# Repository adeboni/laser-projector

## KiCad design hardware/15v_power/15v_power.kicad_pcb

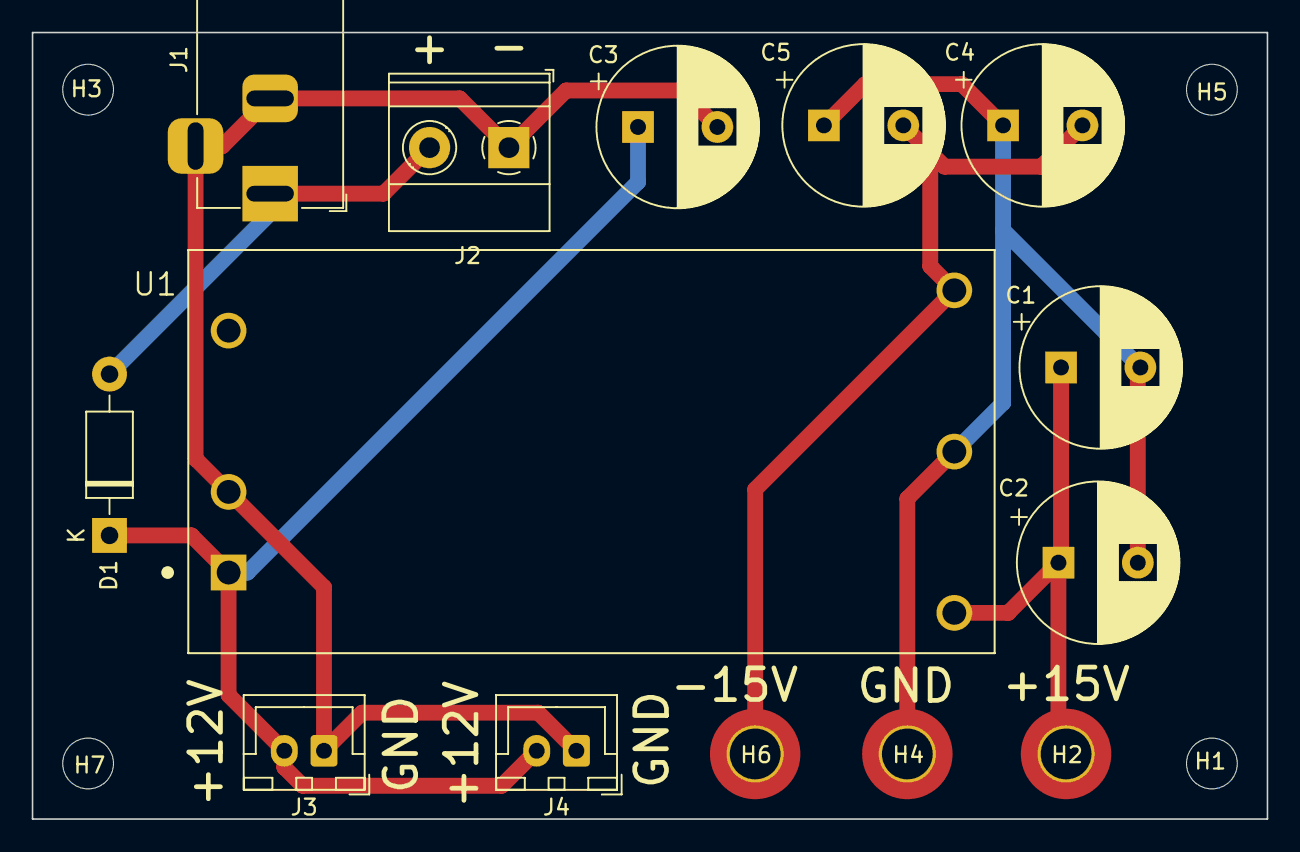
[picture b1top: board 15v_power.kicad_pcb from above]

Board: 2 copper layers, 77.8 x 49.5 mm, 18 parts (0 on the bottom side), 6 nets.

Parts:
C1, C2, C3, C4, C5: 220u; CP_Radial_D10.0mm_P5.00mm
D1: 1N4007; D_DO-41_SOD81_P10.16mm_Horizontal
H1, H3, H5, H7: MountingHole; MountingHole_3.2mm_M3
H2, H4, H6: MountingHole_Pad; MountingHole_3.2mm_M3_ISO7380_Pad_TopBottom
J1: Barrel_Jack_Switch; BarrelJack_Horizontal
J2: Screw_Terminal_01x02; TerminalBlock_Phoenix_MKDS-1,5-2_1x02_P5.00mm_Horizontal
J3, J4: Conn_01x02; JST_XH_B2B-XH-A_1x02_P2.50mm_Vertical
U1: TEN20-2422WIN; CONV_PYBE30-Q24-D12

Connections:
+15V: C1.1, C2.1, H2.1, U1.6 (VOUT+)
-15V: C4.2, C5.2, H6.1, U1.4 (VOUT-)
GND: C1.2, C2.2, C4.1, C5.1, H4.1, U1.5 (CM)
unnamed: C3.1, D1.1 (K), J3.2, J4.2, U1.1 (VIN+)
unnamed: C3.2, J1.2, J1.3, J2.1, J3.1, J4.1, U1.2 (VIN-)
unnamed: D1.2 (A), J1.1, J2.2

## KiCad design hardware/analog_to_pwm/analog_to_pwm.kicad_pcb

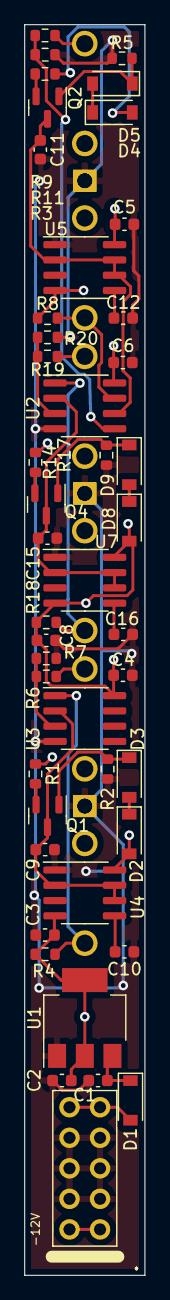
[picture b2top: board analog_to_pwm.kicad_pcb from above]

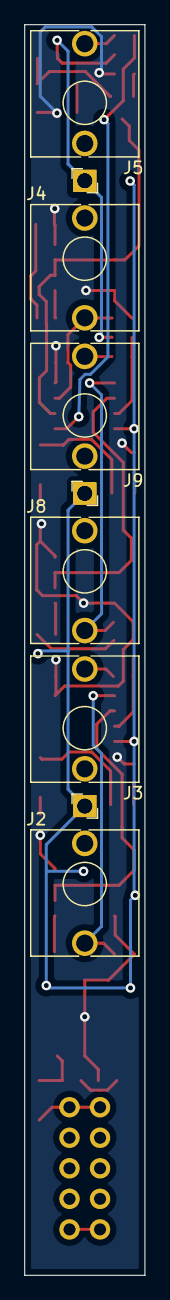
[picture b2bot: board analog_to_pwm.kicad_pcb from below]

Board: 2 copper layers, 10.0 x 104.0 mm, 51 parts (6 on the bottom side), 29 nets.

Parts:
C1, C2: 10u; C_0603_1608Metric
C3, C4, C5, C6, C8, C10, C12, C16: 100n; C_0603_1608Metric
C9, C11, C15: 1.5n; C_0603_1608Metric
D1: SM4007; D_SOD-123
D2, D3, D4, D5, D8, D9: 1N4148W; D_SOD-123
J1: .; Pins_2x05_2.54mm_TH_Europower
J2, J3, J4, J5, J8, J9: JACK; Jack_3.5mm_QingPu_WQP-PJ398SM_Vertical_CircularHoles
Q1, Q2, Q4: MMBT3906; SOT-23
R1, R2, R3, R5, R14, R17: 1k; R_0603_1608Metric
R4, R8, R18: 2.2k; R_0603_1608Metric
R6, R9, R19: 10k; R_0603_1608Metric
R7, R11, R20: 51k; R_0603_1608Metric
U1: LM1117-5.0; SOT-223-3_TabPin2
U2, U3: LM393; SOIC-8_3.9x4.9mm_P1.27mm
U4, U5, U7: NE555D; SOIC-8_3.9x4.9mm_P1.27mm

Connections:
+5V: C2.1, C3.1, C4.1, C5.1, C6.1, C8.1, D2.2 (A), D4.2 (A), D8.2 (A), R1.1, R3.1, R4.1, R8.1, R14.1, R18.1, U1.2 (VO), U2.8 (V+), U3.8 (V+), U4.4 (R), U4.8 (VCC), U5.4 (R), U5.8 (VCC), U7.4 (R), U7.8 (VCC)
GND: C1.2, C2.2, C3.2, C4.2, C5.2, C6.2, C8.2, C9.2, C10.1, C11.2, C12.1, C15.2, C16.1, J1.3, J1.4, J1.5, J1.6, J1.7, J1.8, J2.S, J3.S, J4.S, J5.S, J8.S, J9.S, R2.2, R5.2, R7.2, R11.2, R17.2, R20.2, U1.1 (GND), U2.4 (V-), U3.4 (V-), U4.1 (GND), U5.1 (GND), U7.1 (GND)
unnamed: C1.1, D1.1 (K), U1.3 (VI)
unnamed: C9.1, Q1.3 (C), U3.2 (-), U4.2 (TR), U4.6 (THR), U4.7 (DIS)
unnamed: C10.2, U4.5 (CV)
unnamed: C11.1, Q2.3 (C), U2.6 (_), U5.2 (TR), U5.6 (THR), U5.7 (DIS)
unnamed: C12.2, U5.5 (CV)
unnamed: C15.1, Q4.3 (C), U2.2 (-), U7.2 (TR), U7.6 (THR), U7.7 (DIS)
unnamed: C16.2, U7.5 (CV)
unnamed: D1.2 (A), J1.1, J1.2
unnamed: D2.1 (K), D3.2 (A)
unnamed: D3.1 (K), Q1.1 (B), R2.1
unnamed: D4.1 (K), D5.2 (A)
unnamed: D5.1 (K), Q2.1 (B), R5.1
unnamed: D8.1 (K), D9.2 (A)
unnamed: D9.1 (K), Q4.1 (B), R17.1
unnamed: J1.9, J1.10
unnamed: J2.T, R4.2, U3.1
unnamed: J3.T, R6.2
unnamed: J4.T, R8.2, U2.7
unnamed: J5.T, R9.2
unnamed: J8.T, R18.2, U2.1
unnamed: J9.T, R19.2
unnamed: Q1.2 (E), R1.2
unnamed: Q2.2 (E), R3.2
unnamed: Q4.2 (E), R14.2
unnamed: R6.1, R7.1, U3.3 (+)
unnamed: R9.1, R11.1, U2.5 (+)
unnamed: R19.1, R20.1, U2.3 (+)

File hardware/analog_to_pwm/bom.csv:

Comment,Designator,Footprint,LCSC Part Number
1k,"R2,R3,R5,R1,R17,R14",R_0603_1608Metric,C21190
1N4148W,"D3,D8,D4,D2,D5,D9",D_SOD-123,C81598
51k,"R11,R7,R20",R_0603_1608Metric,C23196
1.5n,"C9,C11,C15",C_0603_1608Metric,C1595
2.2k,"R8,R18,R4",R_0603_1608Metric,C4190
100n,"C8,C6,C16,C5,C12,C4,C3,C10",C_0603_1608Metric,C14663
10k,"R19,R6,R9",R_0603_1608Metric,C25804
NE555D,"U4,U7,U5",SOIC-8_3.9x4.9mm_P1.27mm,C7593
LM1117-5.0,U1,SOT-223-3_TabPin2,C6187
LM393,"U2,U3",SOIC-8_3.9x4.9mm_P1.27mm,C7955
S9015,"Q2,Q4,Q1",SOT-23,C2149
SM4007,D1,D_SOD-123,C64898
10u,"C2,C1",C_0603_1608Metric,C96446

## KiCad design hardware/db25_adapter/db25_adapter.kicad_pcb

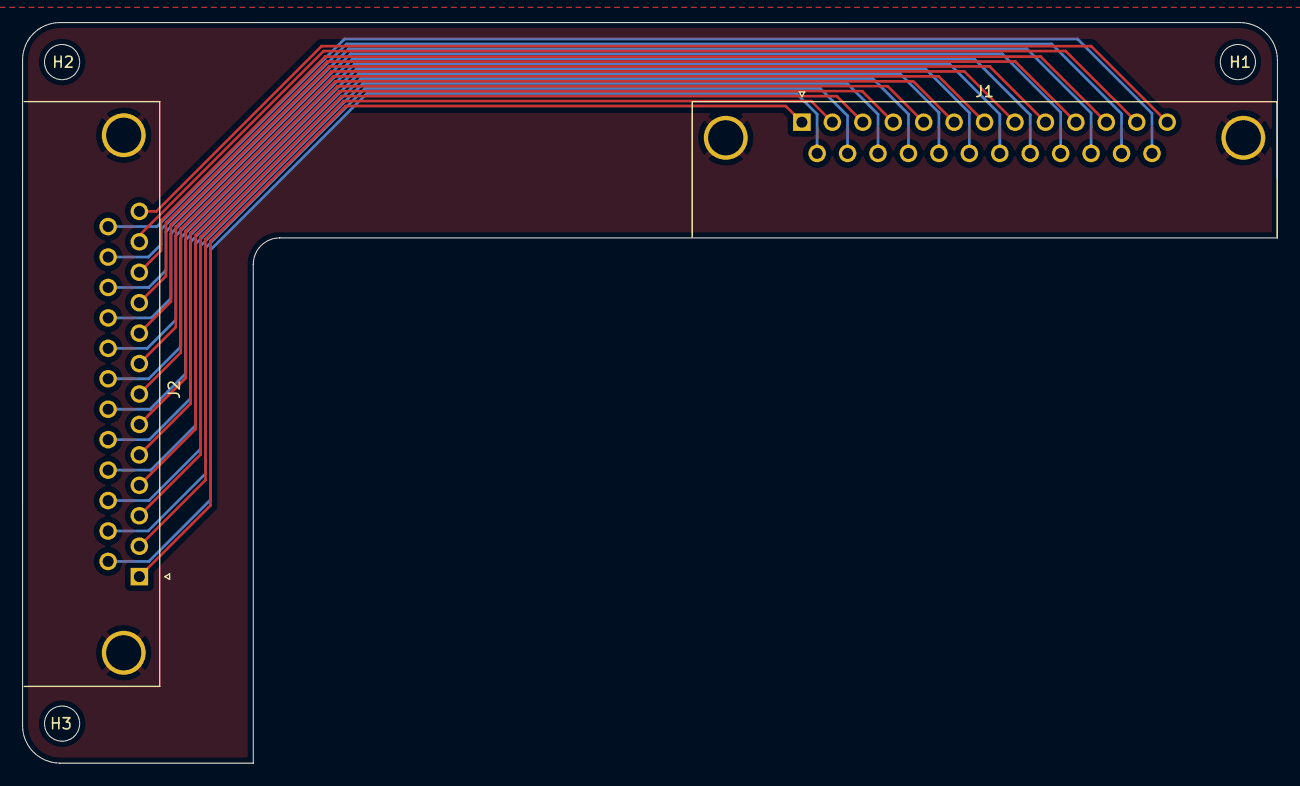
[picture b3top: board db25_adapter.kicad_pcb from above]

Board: 2 copper layers, 114.2 x 67.4 mm, 5 parts (0 on the bottom side), 26 nets.

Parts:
H1, H2, H3: MountingHole; MountingHole_3.2mm_M3
J1: DB25_Male_MountingHoles; DSUB-25_Male_Horizontal_P2.77x2.84mm_EdgePinOffset7.70mm_Ho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
J2: DB25_Female_MountingHoles; DSUB-25_Female_Horizontal_P2.77x2.84mm_EdgePinOffset7.70mm_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

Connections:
GND: J1.0 (PAD), J2.0 (PAD)
unnamed: J1.1, J2.1
unnamed: J1.2, J2.2
unnamed: J1.3, J2.3
unnamed: J1.4, J2.4
unnamed: J1.5, J2.5
unnamed: J1.6, J2.6
unnamed: J1.7, J2.7
unnamed: J1.8, J2.8
unnamed: J1.9, J2.9
unnamed: J1.10, J2.10
unnamed: J1.11, J2.11
unnamed: J1.12, J2.12
unnamed: J1.13, J2.13
unnamed: J1.14, J2.14
unnamed: J1.15, J2.15
unnamed: J1.16, J2.16
unnamed: J1.17, J2.17
unnamed: J1.18, J2.18
unnamed: J1.19, J2.19
unnamed: J1.20, J2.20
unnamed: J1.21, J2.21
unnamed: J1.22, J2.22
unnamed: J1.23, J2.23
unnamed: J1.24, J2.24
unnamed: J1.25, J2.25
